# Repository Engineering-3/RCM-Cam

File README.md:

RCM-Cam
========================

This is a camera module for the RCM Control Stack using the OmniVision OV7725 CMOS chip. Please see [Engineering3](http://engineering3.org/) for more information on the complete RCM Control Stack project.

Repository Contents
-------------------

* **/RCM\-Cam\_v1/RCM-Cam\_v1\_24Jan2012/** Gerbers
* **/RCM\-Cam\_v1/** - BOM

Version History
---------------
* [RCM-Cam_v1](https://github.com/Engineering-3/RCM-Cam/tree/master/RCM-Cam_v1) Inital public version v1

License Information
-------------------
Hardware is released under [Solderpad Hardware License v0.51](http://solderpad.org/licenses/SHL-0.51/).
Distributed as-is; no warranty is given.

Getting Started Help
--------------------
This is a Plug-n-Play board.

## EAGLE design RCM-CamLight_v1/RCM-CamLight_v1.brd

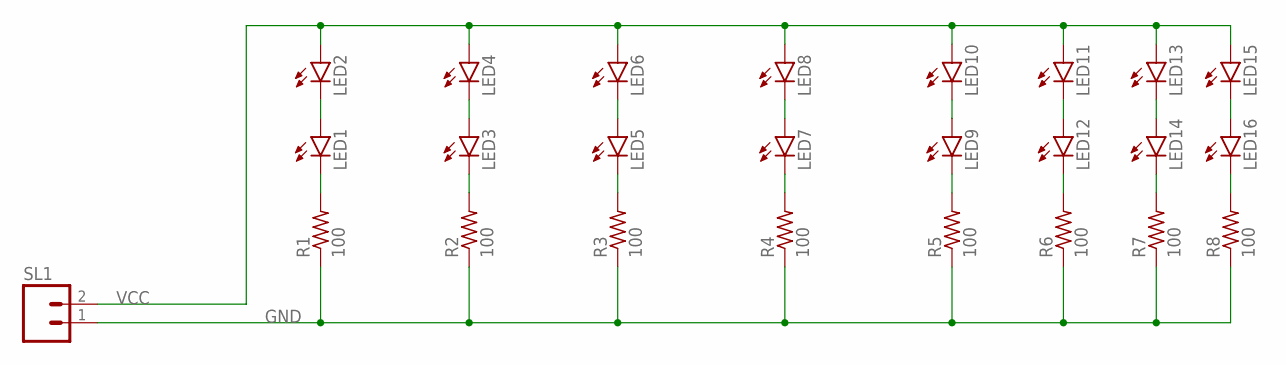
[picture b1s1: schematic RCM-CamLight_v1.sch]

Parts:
LED1, LED2, LED3, LED4, LED5, LED6, LED7, LED8, LED9, LED10, LED11, LED12, LED13, LED14, LED15, LED16: LED3MM
R1, R2, R3, R4, R5, R6, R7, R8: 100; 0204/7
SL1: M02; 02P

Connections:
GND: R1.1, R2.1, R3.1, R4.1, R5.1, R6.1, R7.1, R8.1, SL1.1
unnamed: LED9.A, LED10.K (C)
unnamed: LED12.K (C), R6.2
unnamed: LED1.K (C), R1.2
unnamed: LED1.A, LED2.K (C)
unnamed: LED3.A, LED4.K (C)
unnamed: LED3.K (C), R2.2
unnamed: LED5.K (C), R3.2
unnamed: LED5.A, LED6.K (C)
unnamed: LED7.A, LED8.K (C)
unnamed: LED7.K (C), R4.2
unnamed: LED9.K (C), R5.2
unnamed: LED14.K (C), R7.2
unnamed: LED11.K (C), LED12.A
unnamed: LED16.K (C), R8.2
unnamed: LED15.K (C), LED16.A
unnamed: LED13.K (C), LED14.A
VCC: LED2.A, LED4.A, LED6.A, LED8.A, LED10.A, LED11.A, LED13.A, LED15.A, SL1.2

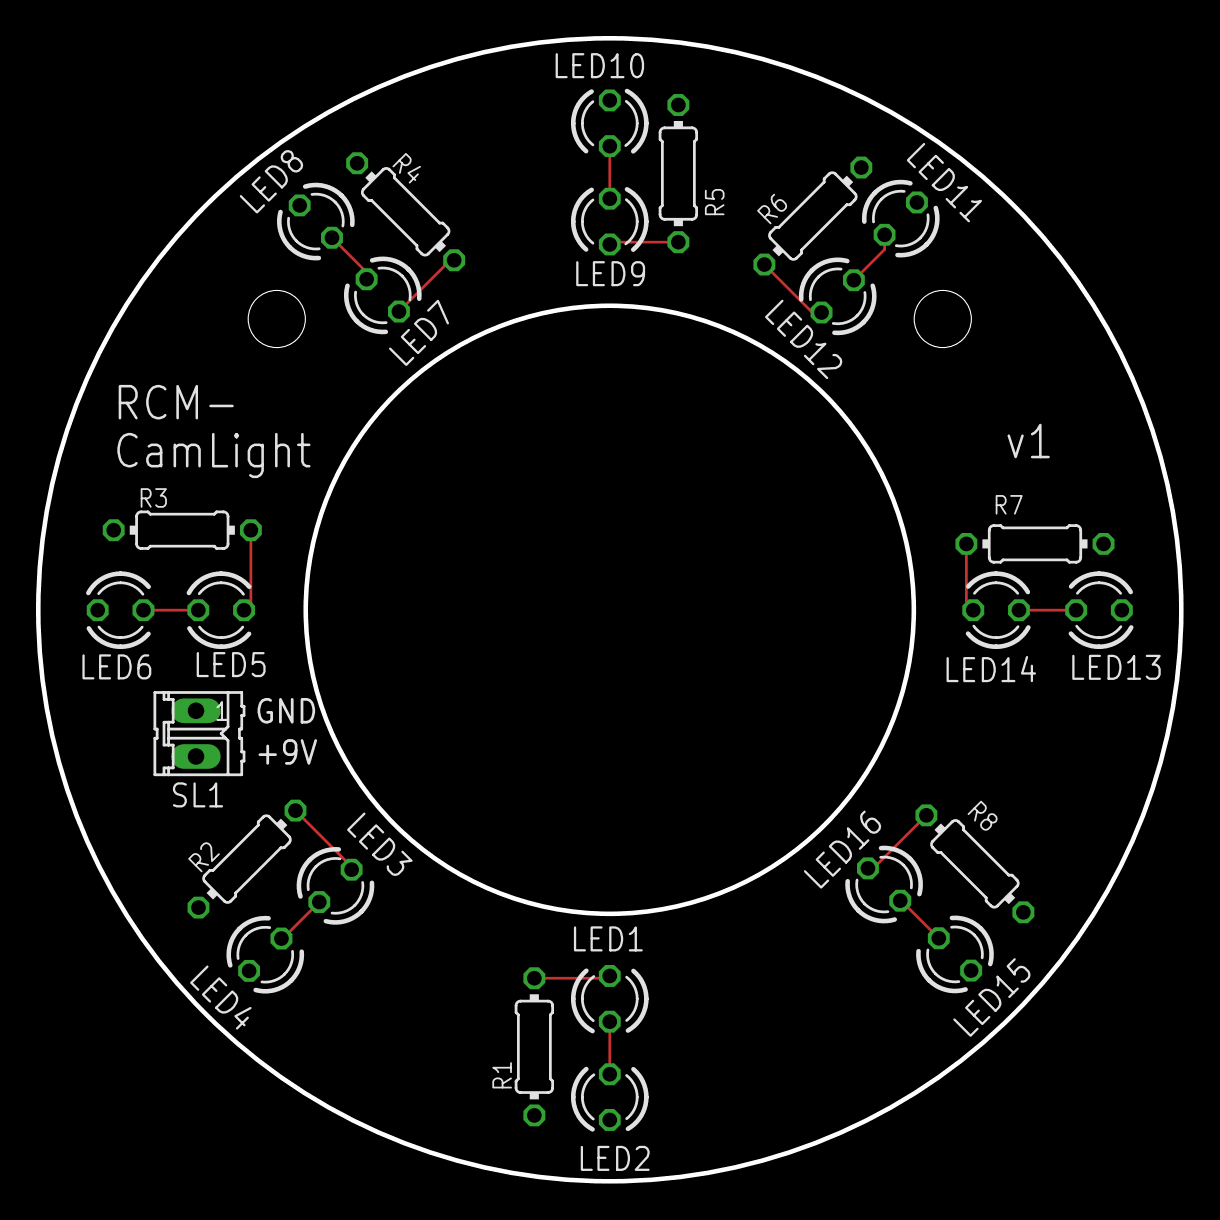
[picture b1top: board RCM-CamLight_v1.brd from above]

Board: 2 copper layers, 63.5 x 63.5 mm, 25 parts (0 on the bottom side), 18 nets.

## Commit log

2015-02-17 Initial file checkin.
2015-02-19 Added readme file.
2016-02-11 Removed incorrect BOM file, replaced with correct BOM file.
2016-08-01 Adding board build readme
2017-03-25 Adding schematic for RCM-CAM v1.
2019-03-22 RCM-CamLight v1 board added
